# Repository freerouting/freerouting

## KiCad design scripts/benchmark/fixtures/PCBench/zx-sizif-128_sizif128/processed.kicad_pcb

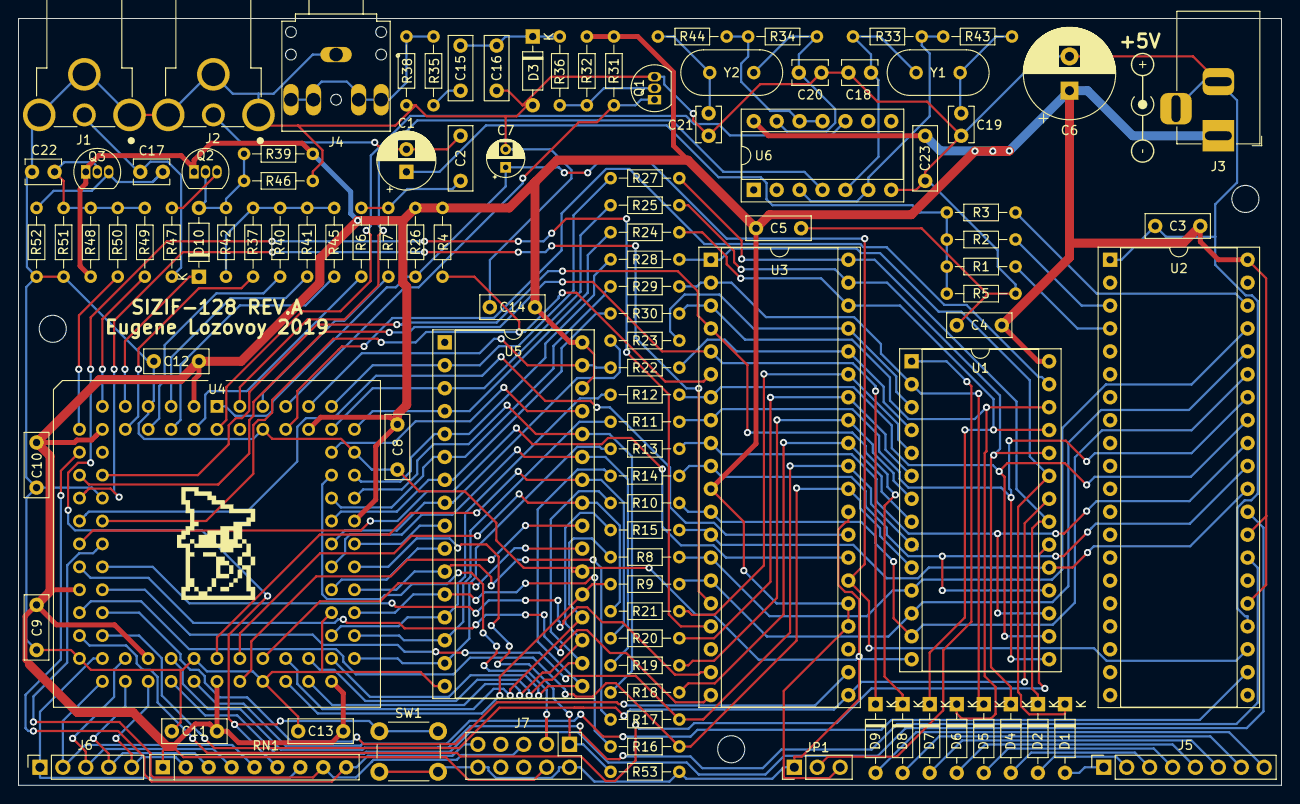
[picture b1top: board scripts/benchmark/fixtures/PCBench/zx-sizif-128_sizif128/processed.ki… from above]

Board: 2 copper layers, 140.0 x 85.0 mm, 112 parts (0 on the bottom side), 120 nets.

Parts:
C1: 10u; CP_Radial_D6.3mm_P2.50mm
C2, C3, C4, C5, C8, C9, C10, C11, C12, C13, C14, C15, C23: 100n; C_Disc_D7.0mm_W2.5mm_P5.00mm
C6: 470u; CP_Radial_D10.0mm_P3.80mm
C7: 10u; CP_Radial_D4.0mm_P2.00mm
C16: 10n; C_Disc_D7.0mm_W2.5mm_P5.00mm
C17: 470p; C_Disc_D3.8mm_W2.6mm_P2.50mm
C18, C20: 33p; C_Disc_D3.8mm_W2.6mm_P2.50mm
C19, C21: 47p; C_Disc_D3.8mm_W2.6mm_P2.50mm
C22: 100p; C_Disc_D3.8mm_W2.6mm_P2.50mm
D1, D2, D4, D5, D6, D7, D8, D9, D10: BAT85; D_DO-35_SOD27_P7.62mm_Horizontal
D3: 1N4148; D_DO-35_SOD27_P7.62mm_Horizontal
H1, H2, H3: MountingHole; MountingHole_3mm
J1, J2: RCJ-013; CUI_RCJ-013
J3: DC-005; BarrelJack_Horizontal
J4: PJ307; SWITCHCRAFT_35RAPC4BHN2
J5: Conn_01x08; PinSocket_1x08_P2.54mm_Vertical
J6: Conn_01x05; PinSocket_1x05_P2.54mm_Vertical
J7: Conn_02x05; PinHeader_2x05_P2.54mm_Vertical
JP1: Jumper_3_Bridged12; PinHeader_1x03_P2.54mm_Vertical
LOGO1: logo; black-mage2
LOGO2: logo; dc_center_positive_big
Q1, Q2, Q3: BC547B; TO-92_Inline
R1, R2, R3, R5, R8, R9, R10, R11, R12, R13, R14, R15, R16, R17, R18, R19, R20, R21, R22, R23, R24, R25, R27, R28, R29, R30, R43, R44: 1k; R_Axial_DIN0204_L3.6mm_D1.6mm_P7.62mm_Horizontal
R4, R49: 2.2k; R_Axial_DIN0204_L3.6mm_D1.6mm_P7.62mm_Horizontal
R6, R40: 4.7k; R_Axial_DIN0204_L3.6mm_D1.6mm_P7.62mm_Horizontal
R7, R31, R36, R37, R38, R53: 10k; R_Axial_DIN0204_L3.6mm_D1.6mm_P7.62mm_Horizontal
R26: 47k; R_Axial_DIN0204_L3.6mm_D1.6mm_P7.62mm_Horizontal
R32: 500k; R_Axial_DIN0204_L3.6mm_D1.6mm_P7.62mm_Horizontal
R33, R34: 1M; R_Axial_DIN0204_L3.6mm_D1.6mm_P7.62mm_Horizontal
R35: 470; R_Axial_DIN0204_L3.6mm_D1.6mm_P7.62mm_Horizontal
R39: 20k; R_Axial_DIN0204_L3.6mm_D1.6mm_P7.62mm_Horizontal
R41: 2.4k; R_Axial_DIN0204_L3.6mm_D1.6mm_P7.62mm_Horizontal
R42: 15k; R_Axial_DIN0204_L3.6mm_D1.6mm_P7.62mm_Horizontal
R45, R50: 8.2k; R_Axial_DIN0204_L3.6mm_D1.6mm_P7.62mm_Horizontal
R46: 12k; R_Axial_DIN0204_L3.6mm_D1.6mm_P7.62mm_Horizontal
R47: 68; R_Axial_DIN0204_L3.6mm_D1.6mm_P7.62mm_Horizontal
R48, R51: 1.2k; R_Axial_DIN0204_L3.6mm_D1.6mm_P7.62mm_Horizontal
R52: 82; R_Axial_DIN0204_L3.6mm_D1.6mm_P7.62mm_Horizontal
RN1: 10k; R_Array_SIP9
SW1: SW_Push; SW_PUSH_6mm
U1: 27C512; DIP-28_W15.24mm_Socket
U2: YM2149; DIP-40_W15.24mm_Socket
U3: Z84C0008PEC; DIP-40_W15.24mm_Socket
U4: EPM7128SLC84-15N; PLCC-84_THT-Socket
U5: 628128; DIP-32_W15.24mm_Socket
U6: 74HCU04; DIP-14_W7.62mm_Socket
Y1: 14.318MHz; Crystal_HC49-U_Vertical
Y2: 16MHz; Crystal_HC49-U_Vertical

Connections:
+5V: C3.2, C4.2, C5.2, C6.1, C8.2, C9.2, C10.2, C11.2, C12.2, C13.2, C14.2, C23.2, J3.1, J7.4, JP1.3, Q2.1, Q3.1, R4.2, R26.1, R31.1, R32.1, R39.2, R48.1, RN1.1, U1.28, U2.25, U2.28, U2.40, U3.11, U3.24, U3.25, U4.3, U4.13, U4.26, U4.38, U4.43, U4.53, U4.66, U4.78, U5.30, U5.32, U6.14
A0: R16.1, U1.10, U3.30, U4.28
A1: R17.1, U1.9, U3.31, U4.27
A2: R18.1, U1.8, U3.32
A3: R19.1, U1.7, U3.33
A4: R20.1, U1.6, U3.34
A5: R21.1, U1.5, U3.35
A6: R22.1, U1.4, U3.36
A7: R23.1, U1.3, U3.37
A8: D7.1, R24.1, U1.25, U3.38
A9: D4.1, R25.1, U1.24, U3.39
A10: D2.1, R27.1, U1.21, U3.40
A11: D1.1, R28.1, U1.23, U3.1
A12: D5.1, R29.1, U1.2, U3.2
A13: D6.1, R30.1, U1.26, U3.3
A14: D8.1, U3.4, U4.17
A15: D9.1, U3.5, U4.16
AY_BC1: U2.29, U4.39
AY_BDIR: U2.27, U4.40
AY_CLK: U2.22, U4.41
BEEPER: R6.1, U4.4
Blue: R37.1, U4.10
Bright: R45.1, U4.6
CHROMA0: R50.1, U4.12
CHROMA1: R49.1, U4.11
CLK14: U4.83, U6.4
CLK16: U4.2, U6.10
CLKCPU: R4.1, U3.6, U4.21
Csync: D10.1, U4.9
D0: R8.1, U1.11, U2.37, U3.14
D1: R9.1, U1.12, U2.36, U3.15
D2: R10.1, U1.13, U2.35, U3.12
D3: R11.1, U1.15, U2.34, U3.8
D4: R12.1, U1.16, U2.33, U3.7
D5: R13.1, U1.17, U2.32, U3.9
D6: R14.1, U1.18, U2.31, U3.10
D7: R15.1, U1.19, U2.30, U3.13
GND: C3.1, C4.1, C5.1, C6.2, C7.2, C8.1, C9.1, C10.1, C11.1, C12.1, C13.1, C14.1, C16.1, C18.1, C19.1, C20.1, C21.1, C22.2, C23.1, D3.2, J1.2, J2.2, J3.2, J3.3, J4.S, J7.2, J7.10, JP1.1, Q1.3, R5.2, R38.2, R46.2, R51.1, R52.1, R53.1, SW1.2, U1.14, U2.1, U2.24, U3.29, U4.7, U4.19, U4.32, U4.42, U4.47, U4.59, U4.72, U4.82, U5.16, U5.22, U6.7
Green: R41.1, U4.5
KD0: J6.1, RN1.7, U4.34
KD1: J6.2, RN1.5, U4.33
KD2: J6.3, RN1.4, U4.36
KD3: J6.4, RN1.3, U4.35
KD4: J6.5, RN1.2, U4.37
unnamed: C1.1, R1.2, R2.2, R3.2, R5.1
unnamed: C2.1, R6.2, R7.2
unnamed: C15.1, R35.2
unnamed: C15.2, C16.2, D3.1, R36.1
unnamed: C17.2, Q3.3, R52.2
unnamed: C18.2, R33.1, U6.5, Y1.1
unnamed: C19.2, R43.1, Y1.2
unnamed: C20.2, R34.1, U6.13, Y2.1
unnamed: C21.2, R44.1, Y2.2
unnamed: C22.1, Q3.2, R48.2, R49.2, R50.2, R51.2
unnamed: D1.2, J5.1
unnamed: D2.2, J5.2
unnamed: D4.2, J5.3
unnamed: D5.2, J5.4
unnamed: D6.2, J5.5
unnamed: D7.2, J5.6
unnamed: D8.2, J5.7
unnamed: D9.2, J5.8
unnamed: D10.2, Q2.2, R39.1, R42.2, R46.1
unnamed: JP1.2, U1.1
unnamed: Q1.2, R32.2, R36.2
unnamed: Q2.3, R47.1
unnamed: R1.1, U2.4
unnamed: R2.1, U2.3
unnamed: R3.1, U2.38
unnamed: R33.2, R43.2, U6.3, U6.6
unnamed: R34.2, R44.2, U6.11, U6.12
unnamed: R37.2, R40.2, R41.2, R42.1, R45.2
RA14: U1.27, U4.80
Red: R40.1, U4.8
SOUND: C1.2, C2.2, J2.1
TAPE_IN: J4.R, J4.RN, J4.T, J4.TN, R35.1, R38.1
TAPE_IN0: Q1.1, R31.2, U4.79
TAPE_OUT: R7.1, U4.81
TCK: J7.1, R53.2, U4.62
TDI: J7.9, RN1.9, U4.14
TDO: J7.3, U4.71
TMS: J7.5, RN1.8, U4.23
VA0: R16.2, U4.58, U5.12
VA1: R17.2, U4.60, U5.11
VA2: R18.2, U4.68, U5.28
VA3: R19.2, U4.63, U5.27
VA4: R20.2, U4.44, U5.26
VA5: R21.2, U4.46, U5.25
VA6: R22.2, U4.77, U5.31
VA7: R23.2, U4.65, U5.8
VA8: R24.2, U4.74, U5.4
VA9: R25.2, U4.76, U5.3
VA10: R27.2, U4.75, U5.2
VA11: R28.2, U4.70, U5.5
VA12: R29.2, U4.69, U5.6
VA13: R30.2, U4.67, U5.7
VA14: U4.61, U5.10
VA15: U4.64, U5.9
VA16: U4.48, U5.23
VD0: R8.2, U4.50, U5.20
VD1: R9.2, U4.49, U5.21
VD2: R10.2, U4.52, U5.18
VD3: R11.2, U4.56, U5.14
VD4: R12.2, U4.57, U5.13
VD5: R13.2, U4.54, U5.15
VD6: R14.2, U4.55, U5.17
VD7: R15.2, U4.51, U5.19
VIDEO: C17.1, J1.1, R47.2
nINT: U3.16, U4.18
nIORQ: U3.20, U4.24
nM1: U3.27, U4.22
nMREQ: U3.19, U4.25
nNMI: RN1.6, SW1.1, U3.17
nRD: U1.22, U3.21, U4.31
nRFSH: U3.28, U4.20
nROMCS: U1.20, U4.30
nRST: C7.1, R26.2, U2.23, U3.26, U4.1
nVRD: U4.45, U5.24
nVWR: U4.73, U5.29
nWR: U3.22, U4.29

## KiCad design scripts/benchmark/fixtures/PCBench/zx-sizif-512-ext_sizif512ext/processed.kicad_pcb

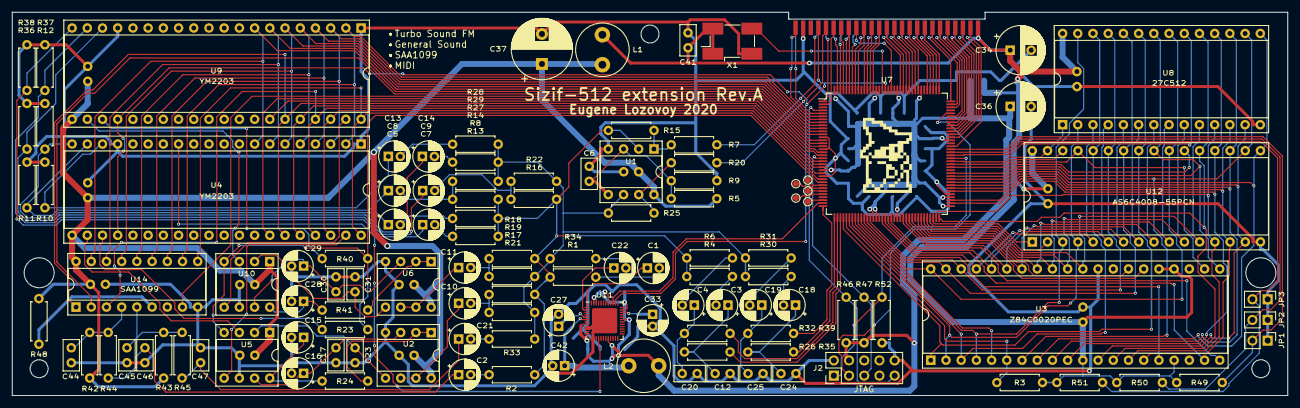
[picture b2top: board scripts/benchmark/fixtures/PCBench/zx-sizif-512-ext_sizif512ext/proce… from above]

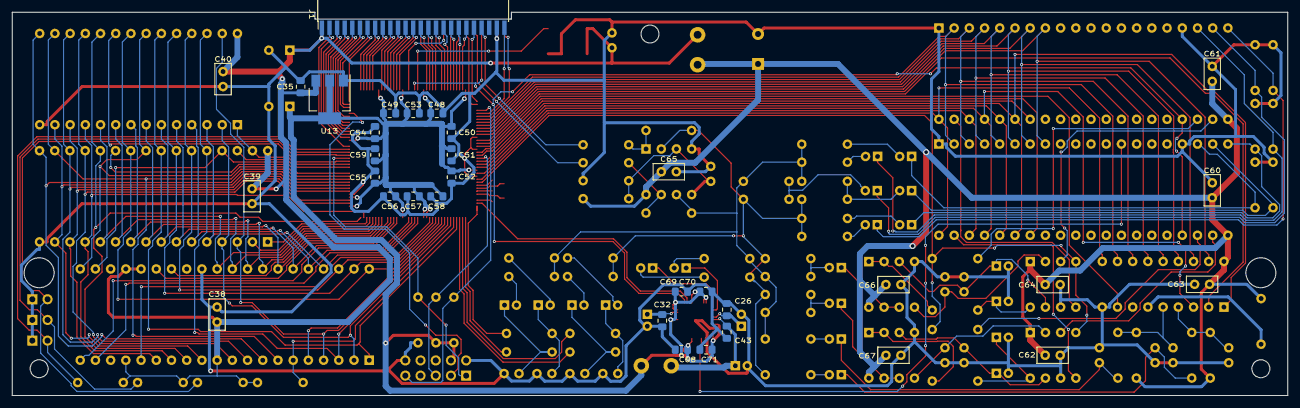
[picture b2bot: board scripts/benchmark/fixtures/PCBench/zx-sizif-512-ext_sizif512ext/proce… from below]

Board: 2 copper layers, 213.0 x 64.0 mm, 156 parts (33 on the bottom side), 179 nets.

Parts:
C1, C2, C3, C4, C5, C7, C8, C9, C10, C11, C13, C14, C15, C16, C18, C19, C21, C22, C27, C28, C29, C33: 10u/16V; CP_Radial_D5.0mm_P2.00mm
C6, C17, C30, C38, C39, C40, C41, C60, C61, C62, C63, C64, C65, C66, C67: 100n; C_Disc_D5.0mm_W2.5mm_P2.50mm
C12, C20, C24, C25: 1n; C_Disc_D5.0mm_W2.5mm_P2.50mm
C23, C31: 2.2n; C_Disc_D5.0mm_W2.5mm_P2.50mm
C26, C32, C35, C43, C48, C49, C50, C51, C52, C53, C54, C55, C56, C57, C58, C59, C68, C69, C70, C71: 100n; C_0805_2012Metric_Pad1.15x1.40mm_HandSolder
C34, C36: 220u/16V; CP_Radial_D8.0mm_P3.50mm
C37: 470u/16V; CP_Radial_D10.0mm_P5.00mm
C42: 47u/16V; CP_Radial_D5.0mm_P2.00mm
C44, C45, C46, C47: 10n; C_Disc_D5.0mm_W2.5mm_P2.50mm
H1, H2: MountingHole; MountingHole_5mm_7mm_fence
H3, H4, H5: MountingHole; MountingHole_3mm
J1: Conn_02x25_Odd_Even; PinHeader_2x25_P1.27mm_Edge_SMD
J2: PinHeader; PinHeader_2x05_P2.54mm_Vertical
JP1, JP2, JP3: Jumper / Pin header 1x2 Pitch=2.54mm; PinHeader_1x02_P2.54mm_Vertical
L1: 220u/1A; L_Radial_D8.7mm_P5.00mm_Fastron_07HCP
L2: 220u/0.2A; L_Radial_D8.7mm_P5.00mm_Fastron_07HCP
LOGO1: graphic; black-mage2
R1, R4, R6, R8, R13, R17, R18, R19, R21, R28, R29, R30, R31, R34: 24k; R_Axial_DIN0207_L6.3mm_D2.5mm_P7.62mm_Horizontal
R2, R15, R25, R33, R46, R47, R48, R49, R50, R51, R52: 10k; R_Axial_DIN0207_L6.3mm_D2.5mm_P7.62mm_Horizontal
R3, R26, R32, R35, R39: 2k; R_Axial_DIN0207_L6.3mm_D2.5mm_P7.62mm_Horizontal
R5, R14, R16, R22, R27: 47k; R_Axial_DIN0207_L6.3mm_D2.5mm_P7.62mm_Horizontal
R7, R20: 2.2k; R_Axial_DIN0207_L6.3mm_D2.5mm_P7.62mm_Horizontal
R9: 27k; R_Axial_DIN0207_L6.3mm_D2.5mm_P7.62mm_Horizontal
R10, R11, R12, R36, R37, R38: 3.3k; R_Axial_DIN0207_L6.3mm_D2.5mm_P7.62mm_Horizontal
R23, R40, R42, R43, R44, R45: 1k; R_Axial_DIN0207_L6.3mm_D2.5mm_P7.62mm_Horizontal
R24, R41: 470; R_Axial_DIN0207_L6.3mm_D2.5mm_P7.62mm_Horizontal
TP1, TP2, TP3, TP4, TP5: TestPoint; TestPoint_Pad_D1.0mm
U1, U2, U6: MCP602; DIP-8_W7.62mm_Socket
U3: Z84C0020PEC; DIP-40_W15.24mm_Socket
U4, U9: YM2203; DIP-40_W15.24mm_Socket
U5, U10: YM3014B; DIP-8_W7.62mm_Socket
U7: EPM3256ATC144; TQFP-144_20x20mm_P0.5mm
U8: 27C512; DIP-28_W15.24mm_Socket
U11: SAM2695; QFN-48-1EP_6x6mm_P0.4mm_EP4.2x4.2mm
U12: AS6C4008-55PCN; DIP-32_W15.24mm_Socket
U13: AMS1117-3.3; SOT-223-3_TabPin2
U14: SAA1099; DIP-18_W7.62mm_Socket
X1: 32MHz; Oscillator_SMD_EuroQuartz_XO91-4Pin_7.0x5.0mm_HandSoldering

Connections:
+3.3VA: C42.1, C43.1, L2.2, U11.6
+3V3: C36.1, C48.1, C49.1, C50.1, C51.1, C52.1, C53.1, C54.1, C55.1, C56.1, C57.1, C58.1, C59.1, C68.1, C69.1, C70.1, C71.1, J2.4, L2.1, R46.2, R47.2, U7.24, U7.50, U7.51, U7.58, U7.73, U7.76, U7.95, U7.115, U7.123, U7.130, U7.144, U11.8, U11.11, U11.12, U11.20, U11.31, U11.35, U11.41, U11.46, U11.47, U13.2
+5V: C34.1, C35.2, C38.2, C39.2, C40.2, C41.2, J1.1, J1.2, L1.1, R3.1, R49.1, R50.1, R51.1, U3.11, U3.17, U3.24, U3.25, U8.28, U12.32, U13.3, X1.1, X1.4
+5VA: C37.1, C60.2, C61.2, C62.2, C63.2, C64.2, C65.2, C66.2, C67.2, L1.2, R5.2, R42.2, R43.2, R48.2, U1.8, U2.8, U4.21, U5.1, U6.8, U9.21, U10.1, U14.18
/A0: J1.35, U7.140
/A1: J1.33, U7.138
/A2: J1.32, U7.136
/A3: J1.31, U7.137
/A4: J1.30, U7.133
/A5: J1.36, U7.139
/A6: J1.29, U7.134
/A7: J1.28, U7.131
/A8: J1.6, U7.97
/A9: J1.9, U7.102
/A10: J1.11, U7.106
/A11: J1.10, U7.101
/A12: J1.8, U7.99
/A13: J1.20, U7.113
/A14: J1.24, U7.119
/A15: J1.23, U7.120
/AA0: U4.37, U7.23, U9.37, U14.3
/AD0: U4.40, U7.27, U9.40, U14.10
/AD1: U4.2, U7.7, U9.2, U14.11
/AD2: U4.3, U7.8, U9.3, U14.12
/AD3: U4.4, U7.9, U9.4, U14.13
/AD4: U4.5, U7.10, U9.5, U14.14
/AD5: U4.6, U7.11, U9.6, U14.15
/AD6: U4.7, U7.12, U9.7, U14.16
/AD7: U4.8, U7.14, U9.8, U14.17
/AY_A1: C5.1, R12.2, U4.20
/AY_A2: C7.1, R38.2, U9.20
/AY_B1: C8.1, R11.2, U4.19
/AY_B2: C9.1, R37.2, U9.19
/AY_C1: C13.1, R10.2, U4.18
/AY_C2: C14.1, R36.2, U9.18
/BUS0: J1.49, U7.5
/BUS1: J1.50, U7.6
/CFG0: JP1.2, R49.2, U7.92
/CFG1: JP2.2, R50.2, U7.91
/CFG2: JP3.2, R51.2, U7.90
/CLK32: U7.128, X1.3
/CLKCPU: J1.34, U7.125
/D0: J1.37, U7.142
/D1: J1.38, U7.141
/D2: J1.39, U7.143
/D3: J1.22, U7.117
/D4: J1.21, U7.118
/D5: J1.18, U7.111
/D6: J1.16, U7.109
/D7: J1.14, U7.107
/FM1: C10.1, U2.6, U2.7
/FM2: C11.1, U6.6, U6.7
/FM_ENA: R23.2, R40.2, U5.4, U7.28, U10.4
/GA0: U3.30, U7.68, U8.10, U12.12
/GA1: U3.31, U7.67, U8.9, U12.11
/GA2: U3.32, U7.66, U8.8, U12.10
/GA3: U3.33, U7.65, U8.7, U12.9
/GA4: U3.34, U7.62, U8.6, U12.8
/GA5: U3.35, U7.60, U8.5, U12.7
/GA6: U3.36, U7.55, U8.4, U12.6
/GA7: U3.37, U7.53, U8.3, U12.5
/GA8: U3.38, U7.48, U8.25, U12.27
/GA9: U3.39, U7.47, U8.24, U12.26
/GA10: U3.40, U7.46, U8.21, U12.23
/GA11: U3.1, U7.40, U8.23, U12.25
/GA12: U3.2, U7.42, U8.2, U12.4
/GA13: U3.3, U7.43, U8.26, U12.28
/GA14: U3.4, U7.44, U8.27, U12.3
/GA15: U3.5, U7.45
/GCH0: C3.1, C12.1, R26.1
/GCH1: C4.1, C20.1, R32.1
/GCH2: C18.1, C24.1, R35.1
/GCH3: C19.1, C25.1, R39.1
/GCLK: R3.2, U3.6, U7.41
/GD0: U3.14, U7.71, U8.11, U12.13
/GD1: U3.15, U7.75, U8.12, U12.14
/GD2: U3.12, U7.79, U8.13, U12.15
/GD3: U3.8, U7.80, U8.15, U12.17
/GD4: U3.7, U7.81, U8.16, U12.18
/GD5: U3.9, U7.78, U8.17, U12.19
/GD6: U3.10, U7.74, U8.18, U12.20
/GD7: U3.13, U7.72, U8.19, U12.21
/GDAC0: R26.2, U7.39
/GDAC1: R32.2, U7.38
/GDAC2: R35.2, U7.37
/GDAC3: R39.2, U7.36
/GMA15: U7.87, U8.1, U12.31
/GMA16: U7.69, U12.2
/GMA17: U7.70, U12.1
/GMA18: U7.86, U12.30
/MIDI_CLK: U7.35, U11.39
/MIDI_IN: U4.13, U11.16
/MIDI_L: C1.1, U11.1
/MIDI_R: C22.1, U11.2
/MIX_L: J1.43, R7.1
/MIX_R: J1.42, R20.1
/SAA_CLK: U7.16, U14.8
/SAA_L: C2.1, C46.1, R44.2
/SAA_R: C21.1, C47.1, R45.2
/TCK: J2.1, R52.1, U7.89
/TDI: J2.9, R46.1, U7.4
/TDO: J2.3, U7.104
/TMS: J2.5, R47.1, U7.20
/YM_M: U4.38, U7.25, U9.38
/~ARD: U4.36, U7.22, U9.36
/~AWR: U4.35, U7.21, U9.35, U14.1
/~BUSACK: J1.3, U7.96
/~BUSRQ: J1.5, U7.98
/~GINT: U3.16, U7.49
/~GIORQ: U3.20, U7.56
/~GM1: U3.27, U7.63
/~GMREQ: U3.19, U7.54
/~GRAM: U7.83, U12.22
/~GRD: U3.21, U7.82, U8.22, U12.24
/~GRESET: U3.26, U7.61
/~GROM: U7.88, U8.20
/~GWR: U3.22, U7.84, U12.29
/~HALT: J1.4, U7.93
/~INT: J1.40, U7.2
/~IORQ: J1.13, U7.108
/~IORQGE: J1.19, U7.116
/~M1: J1.25, U7.122
/~MREQ: J1.27, U7.132
/~NMI: J1.41, U7.1
/~RD: J1.17, U7.112
/~RFSH: J1.26, U7.121
/~ROMCSB: J1.12, U7.103
/~RST: J1.44, U4.24, U7.127, U9.24, U11.38
/~SAA_CS: U7.15, U14.2
/~WAIT: J1.7, U7.100
/~WR: J1.15, U7.110
/~YM1_CS: U4.34, U7.18
/~YM2_CS: U7.19, U9.34
GND: C6.1, C12.2, C15.2, C16.2, C17.2, C20.2, C23.2, C24.2, C25.2, C26.2, C27.2, C28.2, C29.2, C30.2, C31.2, C32.2, C33.2, C34.2, C35.1, C36.2, C37.2, C38.1, C39.1, C40.1, C41.1, C42.2, C43.2, C44.2, C45.2, C46.2, C47.2, C48.2, C49.2, C50.2, C51.2, C52.2, C53.2, C54.2, C55.2, C56.2, C57.2, C58.2, C59.2, C60.1, C61.1, C62.1, C63.1, C64.1, C65.1, C66.1, C67.1, C68.2, C69.2, C70.2, C71.2, J1.47, J1.48, J2.2, J2.10, JP1.1, JP2.1, JP3.1, R9.2, R10.1, R11.1, R12.1, R36.1, R37.1, R38.1, R52.2, U1.4, U2.4, U3.29, U4.1, U4.17, U5.6, U6.4, U7.13, U7.17, U7.26, U7.77, U8.14, U9.1, U9.17, U10.6, U11.9, U11.10, U11.13, U11.14, U11.49, U12.16, U13.1, U14.9, X1.2
unnamed: C1.2, R1.2
unnamed: C2.2, R2.2
unnamed: C3.2, R4.2
unnamed: C4.2, R6.2
unnamed: C5.2, R8.2
unnamed: C6.2, R5.1, R9.1, U1.3, U1.5
unnamed: C7.2, R13.2
unnamed: C8.2, R14.2, R27.2
unnamed: C9.2, R16.2, R22.2
unnamed: C10.2, R17.2, R21.2
unnamed: C11.2, R18.2, R19.2
unnamed: C13.2, R28.2
unnamed: C14.2, R29.2
unnamed: C15.1, R24.2, U5.8
unnamed: C16.1, C17.1, U2.3, U5.7
unnamed: C18.2, R30.2
unnamed: C19.2, R31.2
unnamed: C21.2, R33.2
unnamed: C22.2, R34.2
unnamed: C23.1, U2.5, U5.2
unnamed: C26.1, C27.1, U11.5
unnamed: C28.1, R41.2, U10.8
unnamed: C29.1, C30.1, U6.3, U10.7
unnamed: C31.1, U6.5, U10.2
unnamed: C32.1, C33.1, U11.34
unnamed: C44.1, R42.1, R44.1, U14.4
unnamed: C45.1, R43.1, R45.1, U14.5
unnamed: R1.1, R2.1, R4.1, R6.1, R8.1, R13.1, R14.1, R15.1, R16.1, R17.1, R18.1, U1.2
unnamed: R7.2, R15.2, U1.1
unnamed: R19.1, R21.1, R22.1, R25.1, R27.1, R28.1, R29.1, R30.1, R31.1, R33.1, R34.1, U1.6
unnamed: R20.2, R25.2, U1.7
unnamed: R23.1, U4.23
unnamed: R24.1, U2.1, U2.2
unnamed: R40.1, U9.23
unnamed: R41.1, U6.1, U6.2
unnamed: R48.1, U14.6
unnamed: TP1.1, U7.29
unnamed: TP2.1, U7.30
unnamed: TP3.1, U7.31
unnamed: TP4.1, U7.32
unnamed: TP5.1, U7.34
unnamed: U4.22, U5.3
unnamed: U4.39, U5.5
unnamed: U9.22, U10.3
unnamed: U9.39, U10.5

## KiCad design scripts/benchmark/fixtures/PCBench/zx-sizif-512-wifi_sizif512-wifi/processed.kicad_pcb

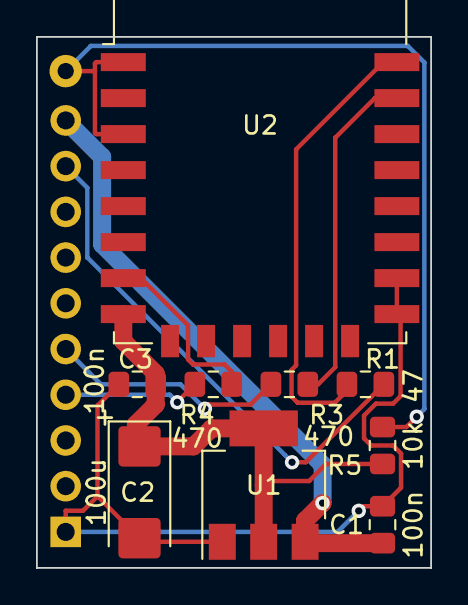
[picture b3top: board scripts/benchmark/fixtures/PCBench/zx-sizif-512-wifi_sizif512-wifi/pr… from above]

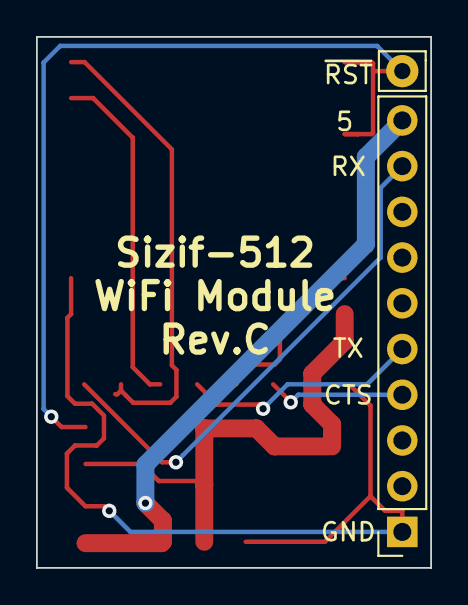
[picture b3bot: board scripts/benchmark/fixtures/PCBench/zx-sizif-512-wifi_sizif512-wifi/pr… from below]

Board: 2 copper layers, 21.9 x 29.5 mm, 11 parts (2 on the bottom side), 10 nets.

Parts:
C1, C3: 100n; C_0805_2012Metric_Pad1.15x1.40mm_HandSolder
C2: 100u; CP_EIA-6032-15_Kemet-U_Pad2.25x2.35mm_HandSolder
J1: Conn_01x10; PinSocket_1x10_P2.54mm_Vertical
R1: 47; C_0805_2012Metric_Pad1.15x1.40mm_HandSolder
R3, R4: 470; C_0805_2012Metric_Pad1.15x1.40mm_HandSolder
R5: 10k; C_0805_2012Metric_Pad1.15x1.40mm_HandSolder
TP1: TestPoint; Pin_D0.9mm_L10.0mm_W2.4mm_FlatFork
U1: AMS1117-3.3; SOT-223-3_TabPin2
U2: ESP-12E

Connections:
+3V3: C2.1, C3.1, R5.2, U1.2, U2.8
+5V: C1.1, J1.10, U1.3
CTS: J1.4, R4.2
GND: C1.2, C2.2, C3.2, J1.1, U1.1, U2.15, U2.16
unnamed: R1.1, U2.22
unnamed: R3.1, U2.21
unnamed: R4.1, U2.7
unnamed: R5.1, TP1.1, U2.1, U2.3
RX: J1.9, R1.2
TX: J1.5, R3.2
